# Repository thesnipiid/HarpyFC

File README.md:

# HarpyFC
**![#f03c15]WARNING :`#f03c15`**
An open source flight controller hardware based on a STM32F722.

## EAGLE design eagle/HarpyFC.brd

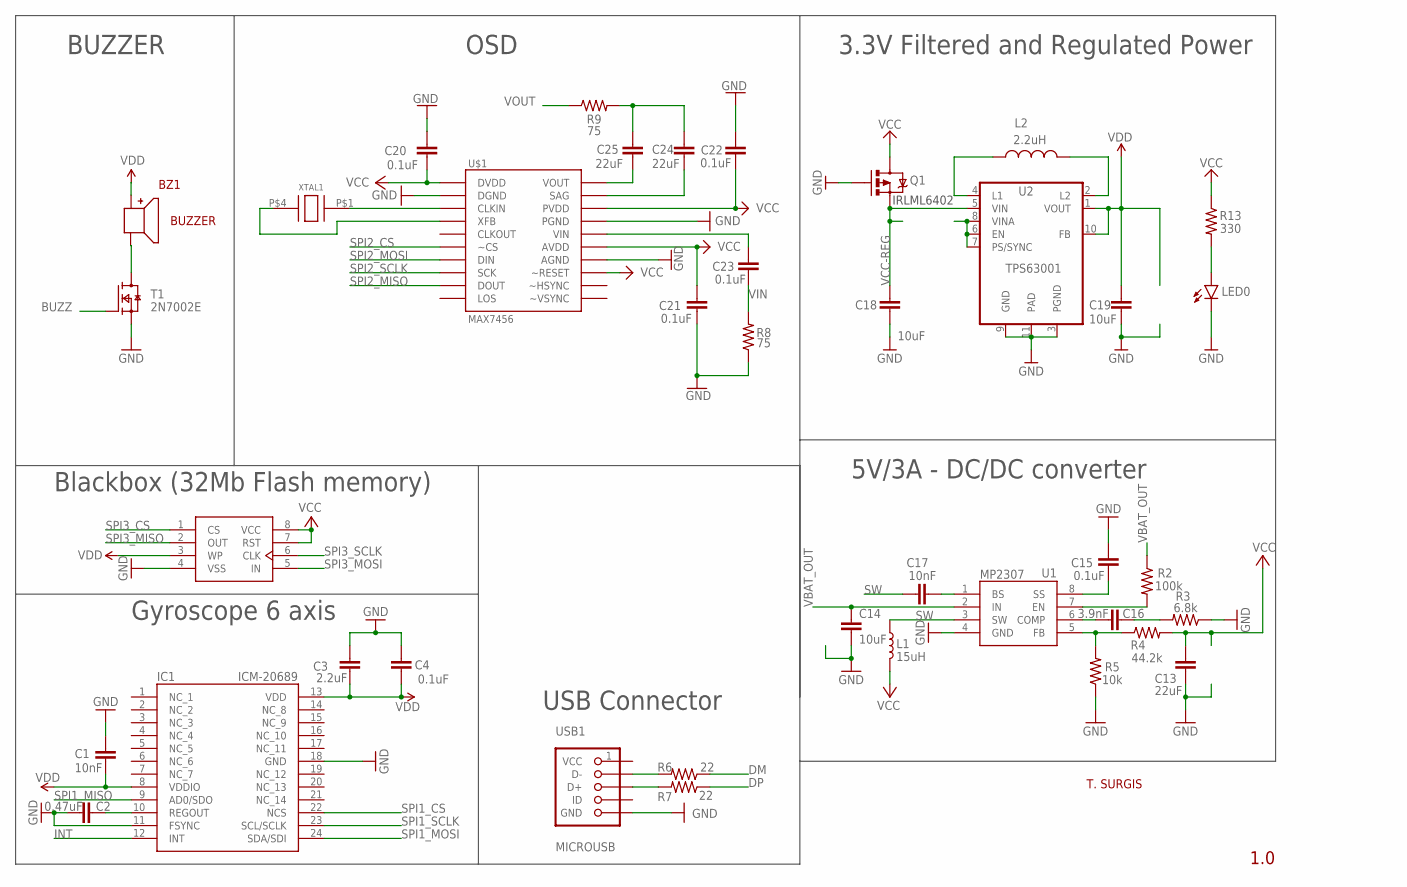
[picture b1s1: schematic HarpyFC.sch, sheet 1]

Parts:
BZ1: BUZZER; CMT-8530S-SMT-TR
C1, C17: 10nF; 0402-TIGHT
C2: 0.47uF; 0402-TIGHT
C3: 2.2uF; 0603
C4, C15, C20, C21, C22, C23: 0.1uF; 0402-TIGHT
C13: 22uF; 0603
C14, C18, C19: 10uF; 0603
C16: 3.9nF; 0402-TIGHT
C24, C25: 22uF; 0805
IC1: ICM-20689; ICM20689
L1: 15uH; MPIL0630
L2: 2.2uH; DFE201612E-INDUCTOR; PARTNO DFE201612E-2R2M-P2
LED0: BLUE; 0805
Q1: MOSFET-PCHANNEL; SOT23-3
R2: 100k; 0402-TIGHT
R3: 6.8k; 0402-TIGHT
R4: 44.2k; 0402-TIGHT
R5: 10k; 0402-TIGHT
R6, R7: 22; 0402-TIGHT
R8, R9: 75; 0402-TIGHT
R13: 330; 0402-TIGHT
T1: 2N7002E; SOT23
U1: MP2307; SOIC8
U2: TPS63001; VSON-N10
U3: MX25L6406EM2I-12G; M25P32; PARTNO MX25L6406EM2I-12G
U$1: MAX7456; TSSOP28
USB1: MICROUSB; 1051330011-SD
XTAL1: CRYSTAL; SX32Y027000BA1T

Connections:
BUZZ: T1.1 (G); also elsewhere on the board
DM: R6.1; also elsewhere on the board
DP: R7.1; also elsewhere on the board
GND: C1.1, C2.1, C3.2, C4.2, C13.2, C14.2, C15.2, C18.2, C19.2, C20.2, C21.2, C22.2, IC1.11 (FSYNC), IC1.18 (GND), LED0.2 (C), Q1.1 (G), R3.1, R5.1, R8.1, T1.2 (S), U1.4 (GND), U2.3 (PGND), U2.9 (GND), U2.11 (PAD), U3.4 (VSS), U$1.4 (DGND), U$1.20 (AGND), U$1.23 (PGND), USB1.5 (GND), USB1.HOLE3 (GND), USB1.HOLE4 (GND), USB1.HOLE5 (GND); also elsewhere on the board
INT: IC1.12 (INT); also elsewhere on the board
L1: L2.P$1 (1), U2.4 (L1)
L2: L2.P$2 (2), U2.2 (L2)
unnamed: C2.2, IC1.10 (REGOUT)
unnamed: R2.2, U1.7 (EN)
unnamed: C15.1, U1.8 (SS)
unnamed: C16.2, U1.6 (COMP)
unnamed: C16.1, R3.2
unnamed: R4.1, R5.2, U1.5 (FB)
unnamed: C17.2, U1.1 (BS)
unnamed: R6.2, USB1.2 (D-)
unnamed: R7.2, USB1.3 (D+)
unnamed: BZ1.P$3, T1.3 (D)
unnamed: U$1.5 (CLKIN), XTAL1.P$1
unnamed: U$1.6 (XFB), XTAL1.P$4
unnamed: C23.2, U$1.22 (VIN)
unnamed: C24.2, U$1.25 (SAG)
unnamed: C25.2, U$1.26 (VOUT)
unnamed: C24.1, C25.1, R9.2
unnamed: LED0.1 (A), R13.2
S$3: C23.1, R8.2
SPI1_CS: IC1.22 (NCS); also elsewhere on the board
SPI1_MISO: IC1.9 (AD0/SDO); also elsewhere on the board
SPI1_MOSI: IC1.24 (SDA/SDI); also elsewhere on the board
SPI1_SCLK: IC1.23 (SCL/SCLK); also elsewhere on the board
SPI2_CS: U$1.8 (~CS); also elsewhere on the board
SPI2_MISO: U$1.11 (DOUT); also elsewhere on the board
SPI2_MOSI: U$1.9 (DIN); also elsewhere on the board
SPI2_SCLK: U$1.10 (SCK); also elsewhere on the board
SPI3_CS: U3.1 (CS); also elsewhere on the board
SPI3_MISO: U3.2 (OUT); also elsewhere on the board
SPI3_MOSI: U3.5 (IN); also elsewhere on the board
SPI3_SCLK: U3.6 (CLK); also elsewhere on the board
SW: C17.1, L1.P$1 (1), U1.3 (SW)
VBAT_OUT: C14.1, R2.1, U1.2 (IN); also elsewhere on the board
VOUT: R9.1; also elsewhere on the board

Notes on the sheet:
Gyroscope 6 axis
5V/3A - DC/DC converter
3.3V Filtered and Regulated Power
MP2307
Blackbox (32Mb Flash memory)
USB Connector
BUZZER
OSD
IRLML6402
1.0
T. SURGIS

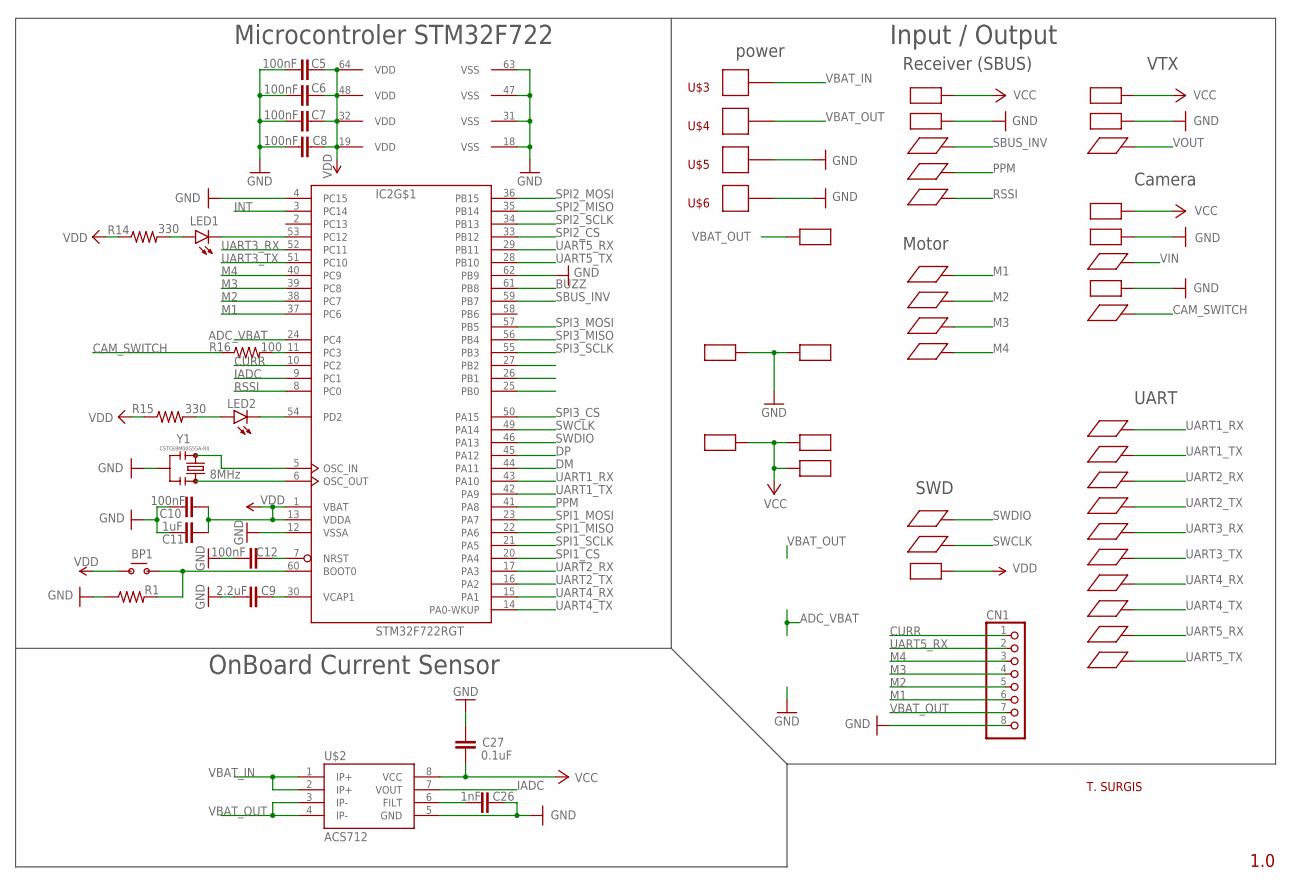
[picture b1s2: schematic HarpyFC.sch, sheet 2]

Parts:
BP1: TL3330
C5, C6, C7, C8, C10, C12: 100nF; 0402-TIGHT
C9: 2.2uF; 0603
C11: 1uF; 0402-TIGHT
C26: 1nF; 0402-TIGHT
C27: 0.1uF; 0402-TIGHT
CN1: JST_8PINJSTSH8; JSTSH8
IC2: STM32F722RGT; LQFP64
LED1, LED2: BLUE; 0805
P$1, P$2, P$3, P$4, P$5, P$6, P$7, P$12, P$13, P$14, P$15, P$16, P$17, P$18, P$19, P$20, P$21, P$22, P$23, P$24, P$25, P$26: SIGNAL_PAD
R1: 0402-TIGHT
R14, R15: 330; 0402-TIGHT
R16: 100; 0402-TIGHT
U$2: ACS712; SO08
U$3, U$4, U$5, U$6: BATTERY_PAD
U$7, U$8, U$9, U$10, U$11, U$17, U$21, U$32, U$33, U$36, U$37, U$38, U$39, U$40: POWER_PAD
Y1: 8MHz; RESONATOR-SMD-3.2X1.3

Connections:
BUZZ: IC2.61 (PB8); also elsewhere on the board
CAM_SWITCH: P$24.P$1, R16.1
CURR: CN1.1, IC2.10 (PC2)
DM: IC2.44 (PA11); also elsewhere on the board
DP: IC2.45 (PA12); also elsewhere on the board
GND: C5.2, C6.2, C7.2, C8.2, C9.2, C10.1, C11.2, C12.1, C26.1, C27.1, CN1.8, IC2.4 (PC15), IC2.12 (VSSA), IC2.18 (VSS), IC2.31 (VSS), IC2.47 (VSS), IC2.62 (PB9), IC2.63 (VSS), R1.1, U$2.5 (GND), U$5.P$1, U$6.P$1, U$8.P$1, U$10.P$1, U$21.P$1, U$32.P$1, U$33.P$1, U$39.P$1, Y1.2; also elsewhere on the board
IADC: IC2.9 (PC1), U$2.7 (VOUT)
INT: IC2.3 (PC14); also elsewhere on the board
M1: CN1.6, IC2.37 (PC6), P$4.P$1
M2: CN1.5, IC2.38 (PC7), P$5.P$1
M3: CN1.4, IC2.39 (PC8), P$6.P$1
M4: CN1.3, IC2.40 (PC9), P$7.P$1
M5: IC2.24 (PC4)
M6: IC2.25 (PB0)
M7: IC2.26 (PB1)
M8: IC2.27 (PB2)
unnamed: IC2.11 (PC3), R16.2
unnamed: IC2.6 (OSC_OUT), Y1.3
unnamed: C9.1, IC2.30 (VCAP1)
unnamed: IC2.5 (OSC_IN), Y1.1
unnamed: BP1.P$4, IC2.60 (BOOT0), R1.2
unnamed: C12.2, IC2.7 (NRST)
unnamed: LED1.1 (A), R14.2
unnamed: IC2.53 (PC12), LED1.2 (C)
unnamed: LED2.1 (A), R15.2
unnamed: C26.2, U$2.6 (FILT)
unnamed: IC2.54 (PD2), LED2.2 (C)
PPM: IC2.41 (PA8), P$22.P$1
RSSI: IC2.8 (PC0), P$23.P$1
SBUS_INV: IC2.59 (PB7), P$3.P$1
SPI1_CS: IC2.20 (PA4); also elsewhere on the board
SPI1_MISO: IC2.22 (PA6); also elsewhere on the board
SPI1_MOSI: IC2.23 (PA7); also elsewhere on the board
SPI1_SCLK: IC2.21 (PA5); also elsewhere on the board
SPI2_CS: IC2.33 (PB12); also elsewhere on the board
SPI2_MISO: IC2.35 (PB14); also elsewhere on the board
SPI2_MOSI: IC2.36 (PB15); also elsewhere on the board
SPI2_SCLK: IC2.34 (PB13); also elsewhere on the board
SPI3_CS: IC2.50 (PA15); also elsewhere on the board
SPI3_MISO: IC2.56 (PB4); also elsewhere on the board
SPI3_MOSI: IC2.57 (PB5); also elsewhere on the board
SPI3_SCLK: IC2.55 (PB3); also elsewhere on the board
SWCLK: IC2.49 (PA14), P$26.P$1
SWDIO: IC2.46 (PA13), P$25.P$1
UART1_RX: IC2.43 (PA10), P$12.P$1
UART1_TX: IC2.42 (PA9), P$13.P$1
UART2_RX: IC2.17 (PA3), P$14.P$1
UART2_TX: IC2.16 (PA2), P$15.P$1
UART3_RX: IC2.52 (PC11), P$16.P$1
UART3_TX: IC2.51 (PC10), P$17.P$1
UART4_RX: IC2.15 (PA1), P$18.P$1
UART4_TX: IC2.14 (PA0-WKUP), P$19.P$1
UART5_RX: CN1.2, IC2.29 (PB11), P$20.P$1
UART5_TX: IC2.28 (PB10), P$21.P$1
VBAT_IN: U$2.1 (IP+), U$2.2 (IP+), U$3.P$1
VBAT_OUT: CN1.7, U$2.3 (IP-), U$2.4 (IP-), U$4.P$1, U$17.P$1; also elsewhere on the board
VIN: P$1.P$1
VOUT: P$2.P$1; also elsewhere on the board

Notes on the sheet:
CSTCE8M00G55A-R0
OnBoard Current Sensor
Microcontroler STM32F722
Input / Output
power
VTX
Camera
Receiver (SBUS)
Motor
UART
SWD
1.0
T. SURGIS

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
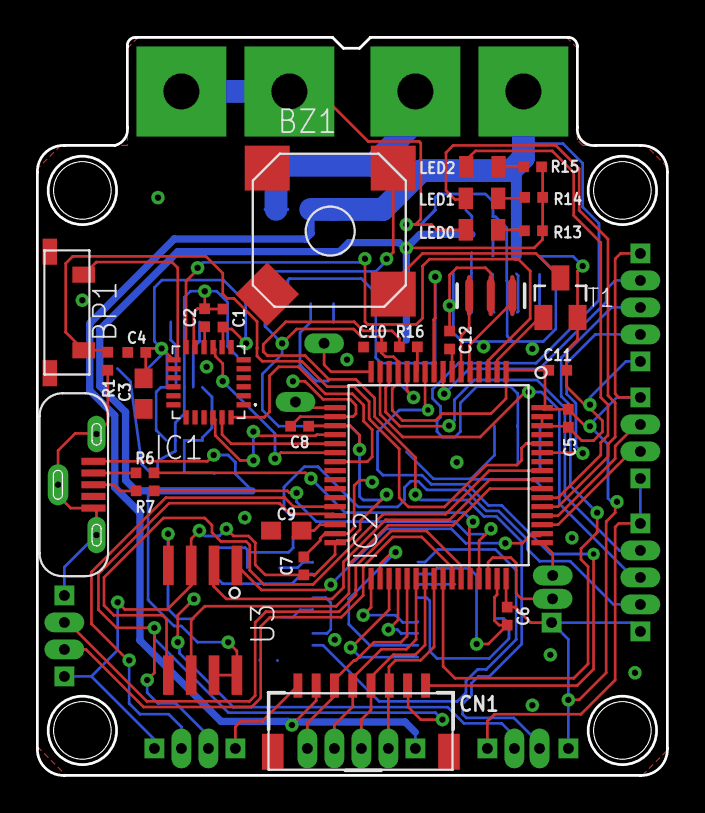
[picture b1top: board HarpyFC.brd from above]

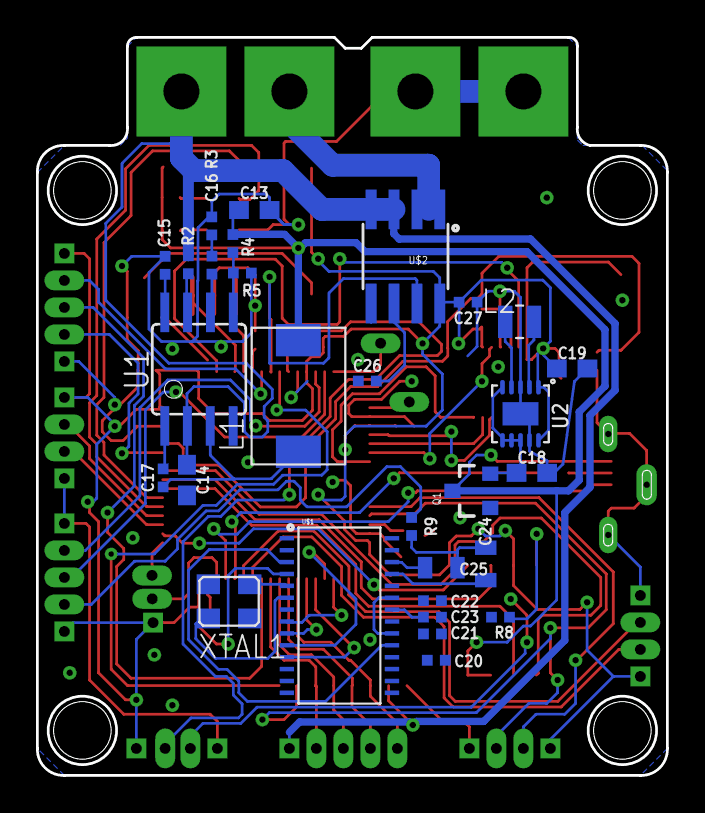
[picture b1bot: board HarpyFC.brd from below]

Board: 2 copper layers, 35.0 x 41.0 mm, 100 parts (29 on the bottom side), 78 nets.

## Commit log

2019-10-27 First commit of the HarpyFC project
2019-10-27 Adding PDF view of schemes
2019-11-02 Routing in process
2019-11-11 outing in progress ..
2019-11-17 routing finished.
2020-02-17 Modification suite a test n1
2020-05-02 last modification, but not implemented on brd
2020-06-21 change README

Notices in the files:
parts and their libraries:
SparkFun-PowerSymbols: Licensing: Creative Commons ShareAlike 4.0 International - https://creativecommons.org/licenses/by-sa/4.0
alienflight: License: CC BY SA
